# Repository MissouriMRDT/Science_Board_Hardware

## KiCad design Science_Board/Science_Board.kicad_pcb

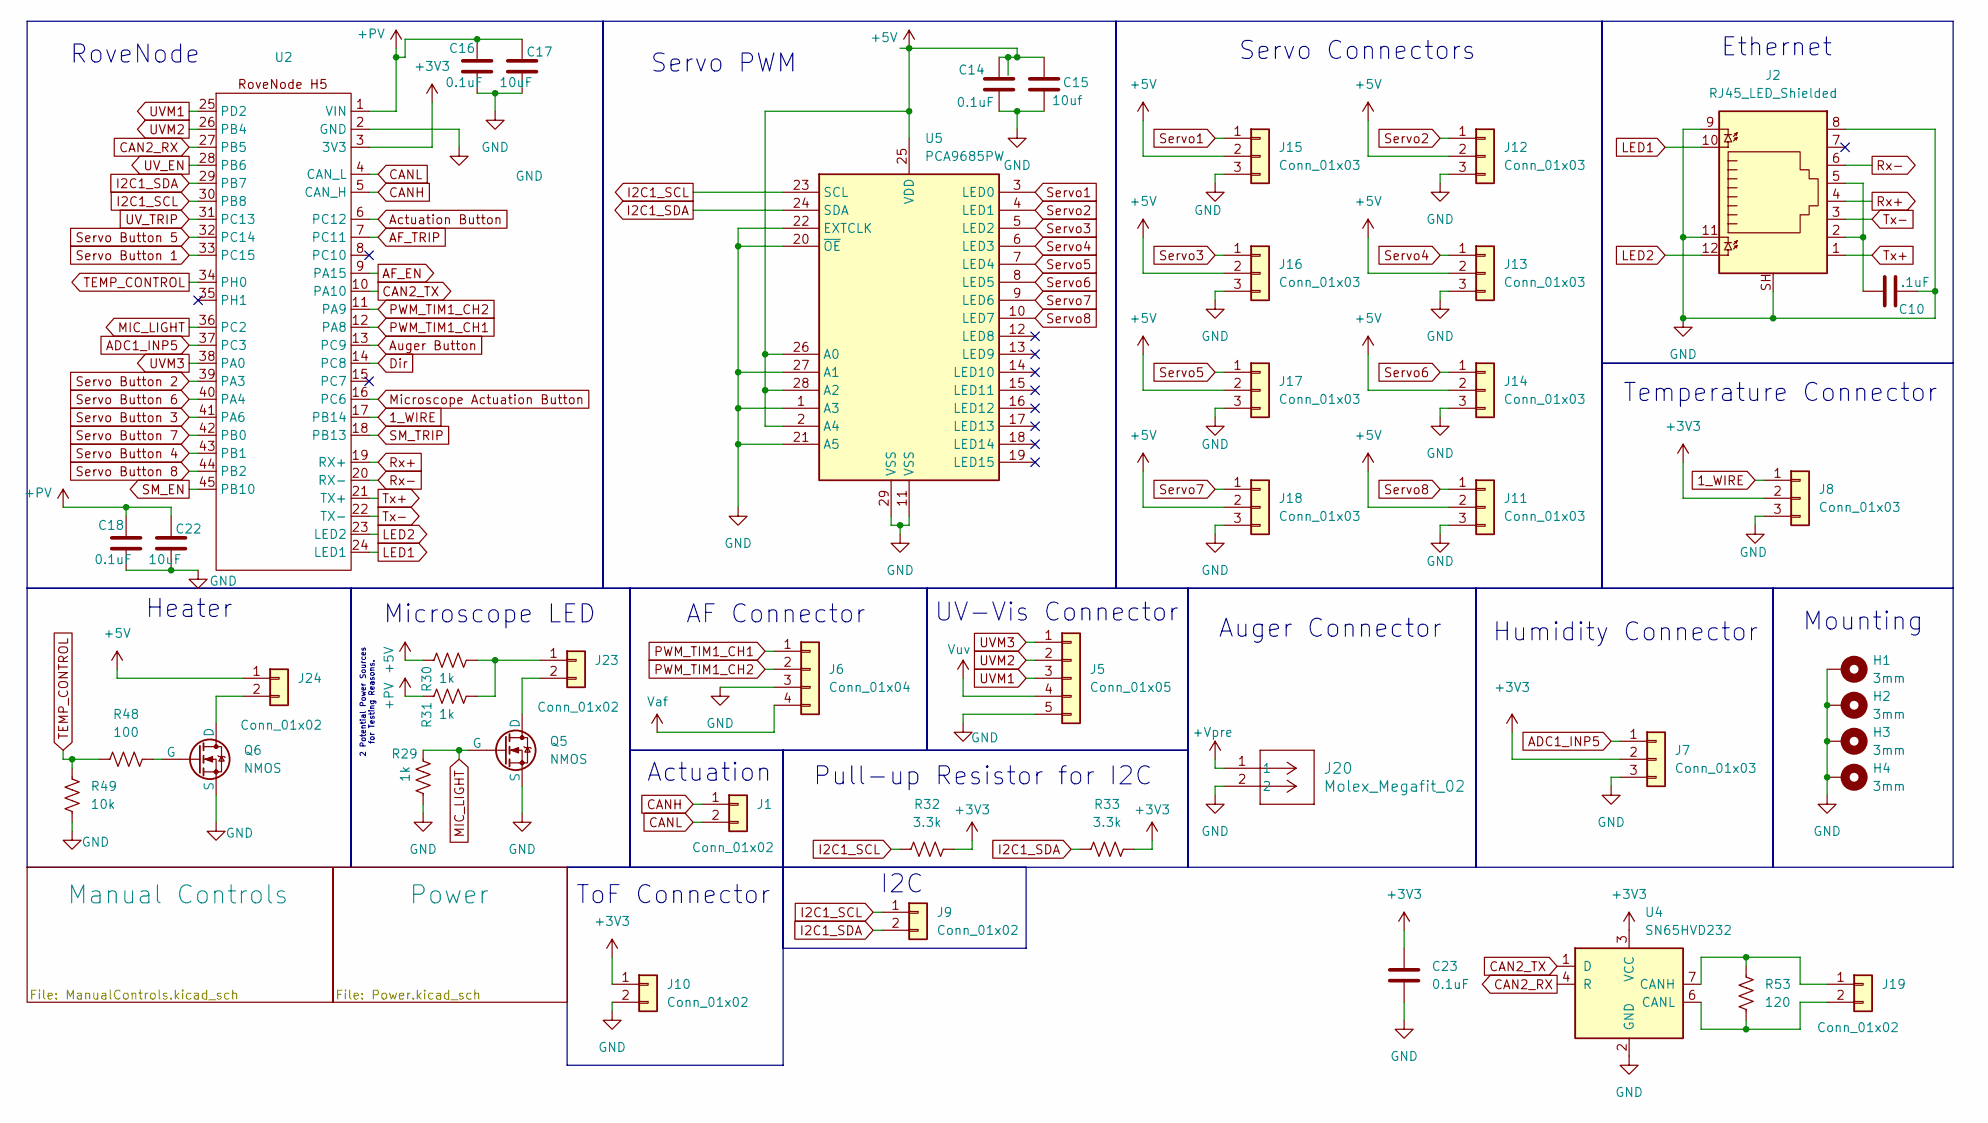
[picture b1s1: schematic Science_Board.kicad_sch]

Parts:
C10: .1uF; C_0603_1608Metric_Pad1.08x0.95mm_HandSolder
C14, C16, C18, C23: 0.1uF; C_0603_1608Metric_Pad1.08x0.95mm_HandSolder
C15: 10uf; C_1210_3225Metric_Pad1.33x2.70mm_HandSolder
C17, C22: 10uF; C_1210_3225Metric_Pad1.33x2.70mm_HandSolder
H1, H2, H3, H4: 3mm; 4_40_Hole_Pad_Via
J1, J9, J10, J19, J23, J24: Conn_01x02; JST_PH_B2B-PH-K_1x02_P2.00mm_Vertical
J2: RJ45_LED_Shielded; RJ45_Teensy
J5: Conn_01x05; JST_PH_B5B-PH-K_1x05_P2.00mm_Vertical
J6: Conn_01x04; JST_PH_B4B-PH-K_1x04_P2.00mm_Vertical
J7, J8, J11, J12, J13, J14, J15, J16, J17, J18: Conn_01x03; JST_PH_B3B-PH-K_1x03_P2.00mm_Vertical
J20: Molex_Megafit_02; MOLEX_MegaFit_02_Horizontal
Q5, Q6: NMOS; SOT-23-3
R29, R30, R31: 1k; R_0603_1608Metric_Pad0.98x0.95mm_HandSolder
R32, R33: 3.3k; R_0603_1608Metric_Pad0.98x0.95mm_HandSolder
R48: 100; R_0603_1608Metric_Pad0.98x0.95mm_HandSolder
R49: 10k; R_0603_1608Metric_Pad0.98x0.95mm_HandSolder
R53: 120; R_0603_1608Metric_Pad0.98x0.95mm_HandSolder
U2: RoveNode_H5
U4: SN65HVD232; SOIC-8_3.9x4.9mm_P1.27mm
U5: PCA9685PW; TSSOP-28_4.4x9.7mm_P0.65mm

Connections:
1_WIRE: J8.1, U2.17 (PB14)
+3V3: C23.1, J7.2, J8.2, J10.1, R32.2, R33.2, U2.3 (3V3), U4.3 (VCC); also elsewhere on the board
+5V: C14.1, C15.2, J11.2, J12.2, J13.2, J14.2, J15.2, J16.2, J17.2, J18.2, J24.1, R30.1, U5.2 (A4), U5.25 (VDD), U5.26 (A0), U5.28 (A2); also elsewhere on the board
+PV: C16.1, C17.2, C18.1, C22.2, R31.1, U2.1 (VIN); also elsewhere on the board
+Vpre: J20.1; also elsewhere on the board
ADC1_INP5: J7.1, U2.37 (PC3)
AF_EN: U2.9 (PA15); also elsewhere on the board
AF_TRIP: U2.7 (PC11); also elsewhere on the board
Actuation Button: U2.6 (PC12); also elsewhere on the board
Auger Button: U2.13 (PC9); also elsewhere on the board
CAN2_RX: U2.27 (PB5), U4.4 (R)
CAN2_TX: U2.10 (PA10), U4.1 (D)
CANH: J1.1, U2.5 (CAN_H)
CANL: J1.2, U2.4 (CAN_L)
Dir: U2.14 (PC8); also elsewhere on the board
GND: C10.2, C14.2, C15.1, C16.2, C17.1, C18.2, C22.1, C23.2, H1.1 (1_1), H2.1 (1_1), H3.1 (1_1), H4.1 (1_1), J2.8, J2.9, J2.11, J2.SH, J5.5, J6.3, J7.3, J8.3, J10.2, J11.3, J12.3, J13.3, J14.3, J15.3, J16.3, J17.3, J18.3, J20.2, Q5.3 (S), Q6.3 (S), R29.2, R49.1, U2.2 (GND), U4.2 (GND), U5.1 (A3), U5.11 (VSS), U5.20 (~OE), U5.21 (A5), U5.22 (EXTCLK), U5.27 (A1), U5.29 (VSS); also elsewhere on the board
I2C1_SCL: J9.1, R32.1, U2.30 (PB8), U5.23 (SCL)
I2C1_SDA: J9.2, R33.1, U2.29 (PB7), U5.24 (SDA)
LED1: J2.10, U2.24 (LED1)
LED2: J2.12, U2.23 (LED2)
MIC_LIGHT: Q5.2 (G), R29.1, U2.36 (PC2)
Microscope Actuation Button: U2.16 (PC6); also elsewhere on the board
unnamed: C10.1, J2.2, J2.5
unnamed: J19.1, R53.1, U4.7 (CANH)
unnamed: J19.2, R53.2, U4.6 (CANL)
unnamed: J23.1, R30.2, R31.2
unnamed: J23.2, Q5.1 (D)
unnamed: J24.2, Q6.1 (D)
unnamed: Q6.2 (G), R48.2
PWM_TIM1_CH1: J6.1, U2.12 (PA8)
PWM_TIM1_CH2: J6.2, U2.11 (PA9)
Rx+: J2.4, U2.19 (RX+)
Rx-: J2.6, U2.20 (RX-)
SM_EN: U2.45 (PB10); also elsewhere on the board
SM_TRIP: U2.18 (PB13); also elsewhere on the board
Servo1: J15.1, U5.3 (LED0)
Servo2: J12.1, U5.4 (LED1)
Servo3: J16.1, U5.5 (LED2)
Servo4: J13.1, U5.6 (LED3)
Servo5: J17.1, U5.7 (LED4)
Servo6: J14.1, U5.8 (LED5)
Servo7: J18.1, U5.9 (LED6)
Servo8: J11.1, U5.10 (LED7)
Servo Button 1: U2.33 (PC15); also elsewhere on the board
Servo Button 2: U2.39 (PA3); also elsewhere on the board
Servo Button 3: U2.41 (PA6); also elsewhere on the board
Servo Button 4: U2.43 (PB1); also elsewhere on the board
Servo Button 5: U2.32 (PC14); also elsewhere on the board
Servo Button 6: U2.40 (PA4); also elsewhere on the board
Servo Button 7: U2.42 (PB0); also elsewhere on the board
Servo Button 8: U2.44 (PB2); also elsewhere on the board
TEMP_CONTROL: R48.1, R49.2, U2.34 (PH0)
Tx+: J2.1, U2.21 (TX+)
Tx-: J2.3, U2.22 (TX-)
UVM1: J5.3, U2.25 (PD2)
UVM2: J5.2, U2.26 (PB4)
UVM3: J5.1, U2.38 (PA0)
UV_EN: U2.28 (PB6); also elsewhere on the board
UV_TRIP: U2.31 (PC13); also elsewhere on the board
Vaf: J6.4; also elsewhere on the board
Vuv: J5.4; also elsewhere on the board

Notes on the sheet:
UV-Vis Connector
Servo Connectors
Auger Connector
Temperature Connector
Servo PWM
ToF Connector
AF Connector
Microscope LED
RoveNode
Heater
Pull-up Resistor for I2C
Ethernet
Mounting
2 Potential Power Sources for Testing Reasons.
Actuation
I2C
Humidity Connector

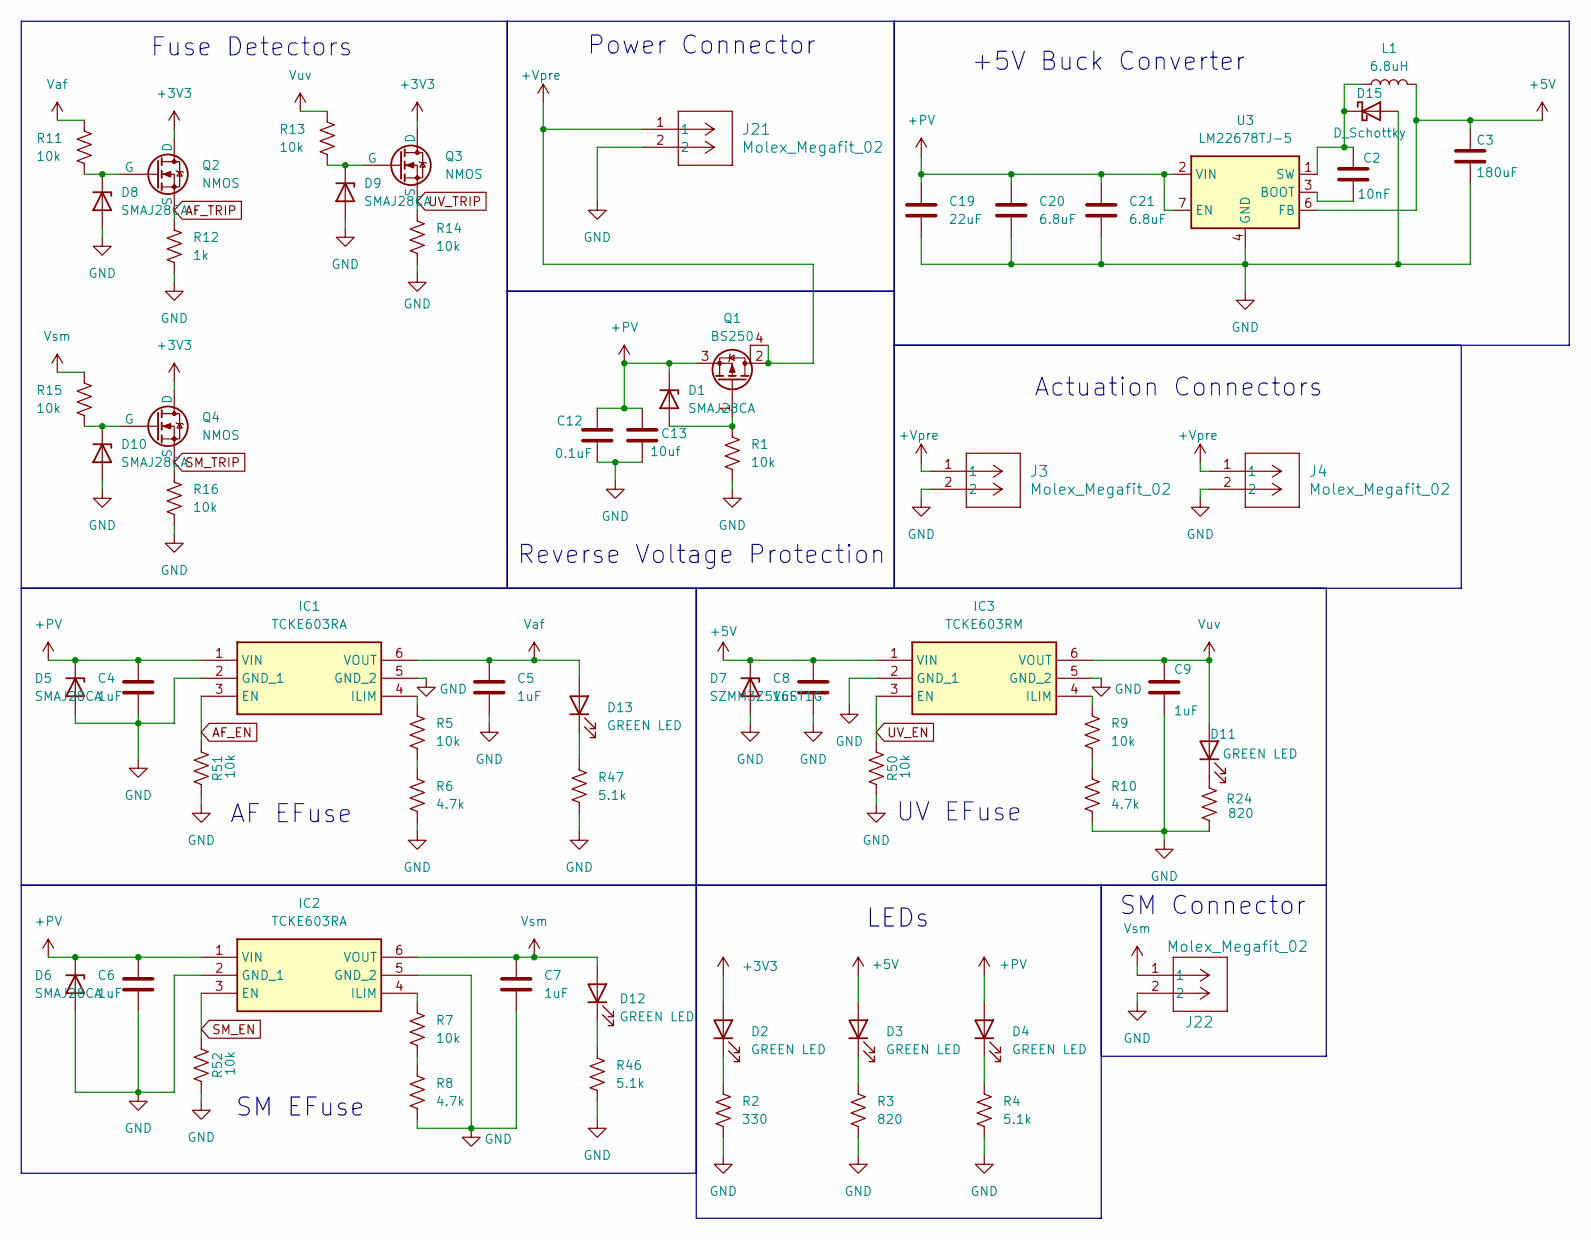
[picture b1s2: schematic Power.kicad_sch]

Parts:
C2: 10nF; C_0603_1608Metric_Pad1.08x0.95mm_HandSolder
C3: 180uF; CAP_EEEFNE181XUL
C4, C5, C6, C7, C8, C9: 1uF; C_0603_1608Metric_Pad1.08x0.95mm_HandSolder
C12: 0.1uF; C_0603_1608Metric_Pad1.08x0.95mm_HandSolder
C13: 10uf; C_1210_3225Metric_Pad1.33x2.70mm_HandSolder
C19: 22uF; C_1210_3225Metric_Pad1.33x2.70mm_HandSolder
C20, C21: 6.8uF; C_1206_3216Metric_Pad1.33x1.80mm_HandSolder
D1, D8, D9, D10: SMAJ28CA; D_SOD-123
D2, D3, D4, D11, D12, D13: GREEN LED; LED_0603_1608Metric_Pad1.05x0.95mm_HandSolder
D5, D6: SMAJ28CA; D_SMA_Handsoldering
D7: SZMM3Z5V6ST1G; D_SOD-323_HandSoldering
D15: D_Schottky; D_SOD-128
IC1, IC2: TCKE603RA; TCKE602RM; Manufacturer_Part_Number TCKE602RM
IC3: TCKE603RM; TCKE602RM; Manufacturer_Part_Number TCKE602RM
J3, J4, J21, J22: Molex_Megafit_02; MOLEX_MegaFit_02_Horizontal
L1: 6.8uH; L_Bourns_SRN8040TA
Q1: BS250; SOT-223
Q2, Q3, Q4: NMOS; SOT-23-3
R1, R5, R7, R9, R11, R13, R14, R15, R16: 10k; R_0603_1608Metric_Pad0.98x0.95mm_HandSolder
R2: 330; R_0603_1608Metric_Pad0.98x0.95mm_HandSolder
R3, R24: 820; R_0603_1608Metric_Pad0.98x0.95mm_HandSolder
R4, R46, R47: 5.1k; R_0603_1608Metric_Pad0.98x0.95mm_HandSolder
R6, R8, R10: 4.7k; R_0603_1608Metric_Pad0.98x0.95mm_HandSolder
R12: 1k; R_0603_1608Metric_Pad0.98x0.95mm_HandSolder
R50, R51, R52: 10k
U3: LM22678TJ-5; TO-263-7_TabPin8

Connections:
+3V3: D2.2 (A), Q2.1 (D), Q3.1 (D), Q4.1 (D); also elsewhere on the board
+5V: C3.1, C8.1, D3.2 (A), D7.1 (K), IC3.1 (VIN), L1.2, U3.6 (FB); also elsewhere on the board
+PV: C4.1, C6.1, C12.1, C13.2, C19.1, C20.1, C21.1, D1.1 (K), D4.2 (A), D5.1 (K), D6.1 (K), IC1.1 (VIN), IC2.1 (VIN), Q1.3 (S), U3.2 (VIN), U3.7 (EN); also elsewhere on the board
+Vpre: J3.1, J4.1, J21.1, Q1.2 (D), Q1.4 (D); also elsewhere on the board
AF_EN: IC1.3 (EN), R51.1; also elsewhere on the board
AF_TRIP: Q2.3 (S), R12.1; also elsewhere on the board
GND: C3.2, C4.2, C5.2, C6.2, C7.2, C8.2, C9.2, C12.2, C13.1, C19.2, C20.2, C21.2, D5.2 (A), D6.2 (A), D7.2 (A), D8.2 (A), D9.2 (A), D10.2 (A), D15.2 (A), IC1.2 (GND_1), IC1.5 (GND_2), IC2.2 (GND_1), IC2.5 (GND_2), IC3.2 (GND_1), IC3.5 (GND_2), J3.2, J4.2, J21.2, J22.2, R1.1, R2.2, R3.2, R4.2, R6.2, R8.2, R10.2, R12.2, R14.2, R16.2, R24.2, R46.2, R47.2, R50.2, R51.2, R52.2, U3.4 (GND), U3.8 (GND); also elsewhere on the board
unnamed: D1.2 (A), Q1.1 (G), R1.2
unnamed: D2.1 (K), R2.1
unnamed: D3.1 (K), R3.1
unnamed: D4.1 (K), R4.1
unnamed: D8.1 (K), Q2.2 (G), R11.2
unnamed: D9.1 (K), Q3.2 (G), R13.2
unnamed: D10.1 (K), Q4.2 (G), R15.2
unnamed: D11.1 (K), R24.1
unnamed: D12.1 (K), R46.1
unnamed: D13.1 (K), R47.1
unnamed: C2.1, D15.1 (K), L1.1, U3.1 (SW)
unnamed: IC1.4 (ILIM), R5.1
unnamed: IC2.4 (ILIM), R7.1
unnamed: IC3.4 (ILIM), R9.1
unnamed: R5.2, R6.1
unnamed: R7.2, R8.1
unnamed: R9.2, R10.1
unnamed: C2.2, U3.3 (BOOT)
SM_EN: IC2.3 (EN), R52.1; also elsewhere on the board
SM_TRIP: Q4.3 (S), R16.1; also elsewhere on the board
UV_EN: IC3.3 (EN), R50.1; also elsewhere on the board
UV_TRIP: Q3.3 (S), R14.1; also elsewhere on the board
Vaf: C5.1, D13.2 (A), IC1.6 (VOUT), R11.1; also elsewhere on the board
Vsm: C7.1, D12.2 (A), IC2.6 (VOUT), J22.1, R15.1
Vuv: C9.1, D11.2 (A), IC3.6 (VOUT), R13.1; also elsewhere on the board

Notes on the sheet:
Reverse Voltage Protection
Fuse Detectors
Power Connector
+5V Buck Converter
AF EFuse
SM EFuse
UV EFuse
Actuation Connectors
LEDs
SM Connector

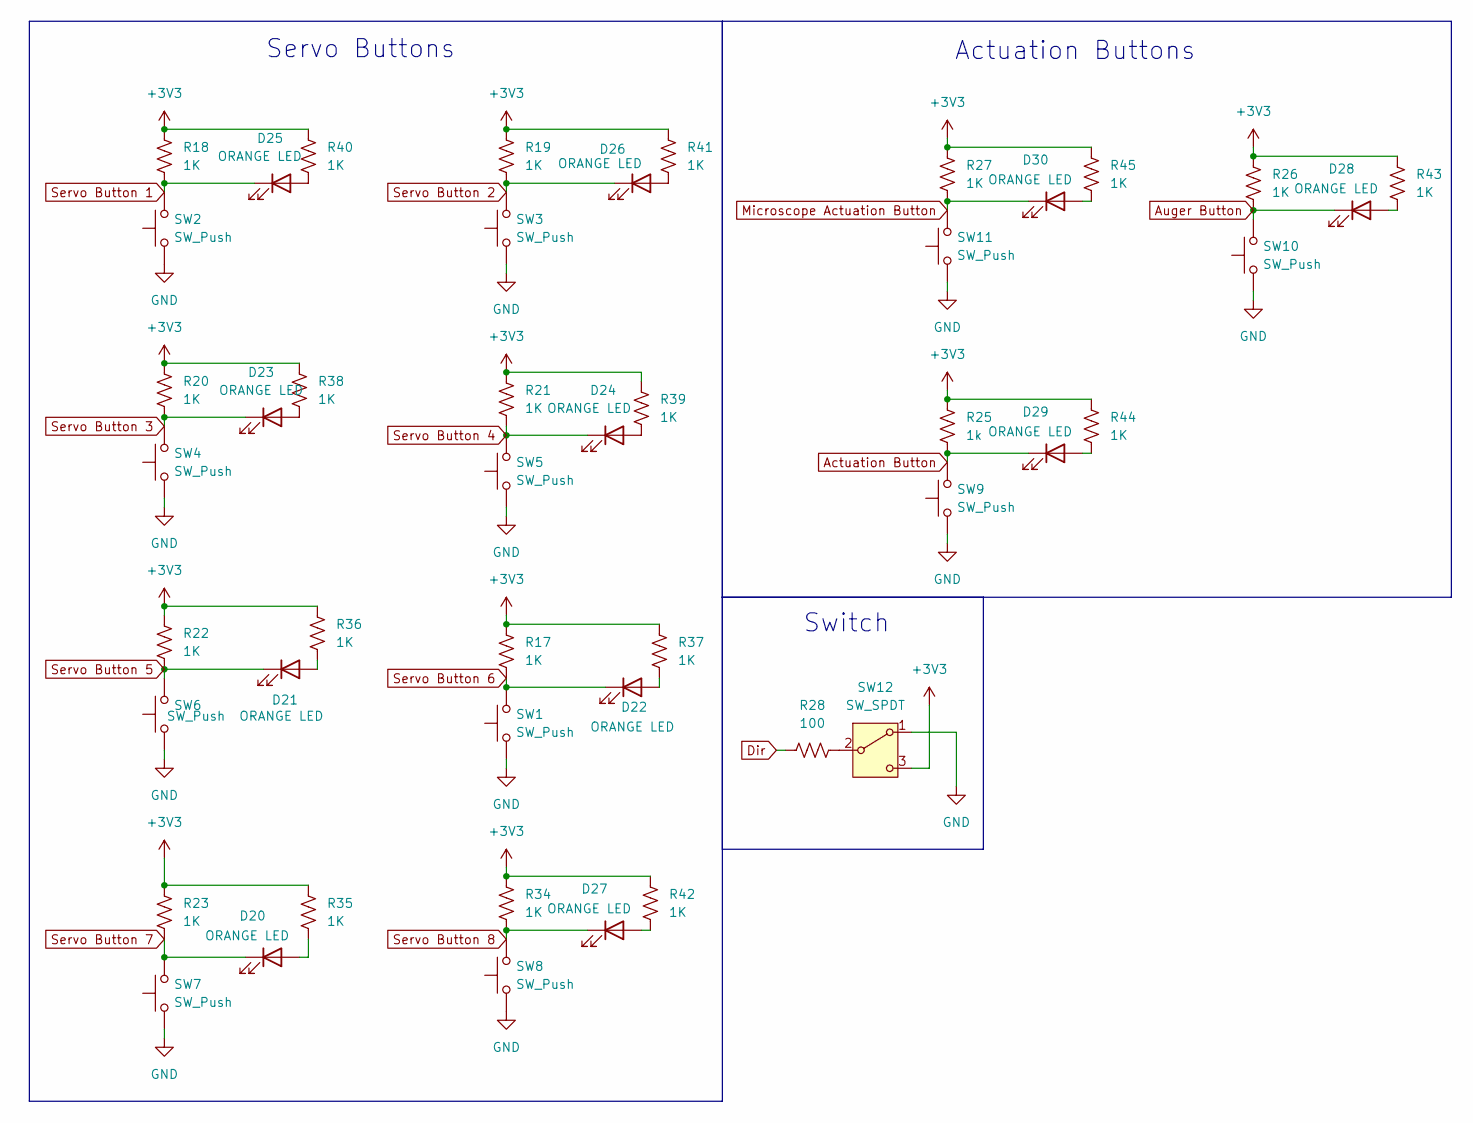
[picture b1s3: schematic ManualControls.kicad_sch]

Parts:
D20, D21, D22, D23, D24, D25, D26, D27, D28, D29, D30: ORANGE LED; LED_0603_1608Metric_Pad1.05x0.95mm_HandSolder
R17, R18, R19, R20, R21, R22, R23, R26, R27, R34, R35, R36, R37, R38, R39, R40, R41, R42, R43, R44, R45: 1K; R_0603_1608Metric_Pad0.98x0.95mm_HandSolder
R25: 1k; R_0603_1608Metric_Pad0.98x0.95mm_HandSolder
R28: 100; R_0603_1608Metric_Pad0.98x0.95mm_HandSolder
SW1, SW2, SW3, SW4, SW5, SW6, SW7, SW8, SW9, SW10, SW11: SW_Push; SW_SPST_TL3305A
SW12: SW_SPDT; SW_Slide_SPDT_Straight_CK_OS102011MS2Q

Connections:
+3V3: R17.1, R18.1, R19.1, R20.1, R21.1, R22.1, R23.1, R25.1, R26.1, R27.1, R34.1, R35.1, R36.1, R37.1, R38.1, R39.1, R40.1, R41.1, R42.1, R43.1, R44.1, R45.1, SW12.3 (C); also elsewhere on the board
Actuation Button: D29.1 (K), R25.2, SW9.2; also elsewhere on the board
Auger Button: D28.1 (K), R26.2, SW10.2; also elsewhere on the board
Dir: R28.1; also elsewhere on the board
GND: SW1.1, SW2.1, SW3.1, SW4.1, SW5.1, SW6.1, SW7.1, SW8.1, SW9.1, SW10.1, SW11.1, SW12.1 (A); also elsewhere on the board
Microscope Actuation Button: D30.1 (K), R27.2, SW11.2; also elsewhere on the board
unnamed: D20.2 (A), R35.2
unnamed: D21.2 (A), R36.2
unnamed: D22.2 (A), R37.2
unnamed: D23.2 (A), R38.2
unnamed: D24.2 (A), R39.2
unnamed: D25.2 (A), R40.2
unnamed: D26.2 (A), R41.2
unnamed: D27.2 (A), R42.2
unnamed: D28.2 (A), R43.2
unnamed: D29.2 (A), R44.2
unnamed: D30.2 (A), R45.2
unnamed: R28.2, SW12.2 (B)
Servo Button 1: D25.1 (K), R18.2, SW2.2; also elsewhere on the board
Servo Button 2: D26.1 (K), R19.2, SW3.2; also elsewhere on the board
Servo Button 3: D23.1 (K), R20.2, SW4.2; also elsewhere on the board
Servo Button 4: D24.1 (K), R21.2, SW5.2; also elsewhere on the board
Servo Button 5: D21.1 (K), R22.2, SW6.2; also elsewhere on the board
Servo Button 6: D22.1 (K), R17.2, SW1.2; also elsewhere on the board
Servo Button 7: D20.1 (K), R23.2, SW7.2; also elsewhere on the board
Servo Button 8: D27.1 (K), R34.2, SW8.2; also elsewhere on the board

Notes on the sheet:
Actuation Buttons
Switch
Servo Buttons

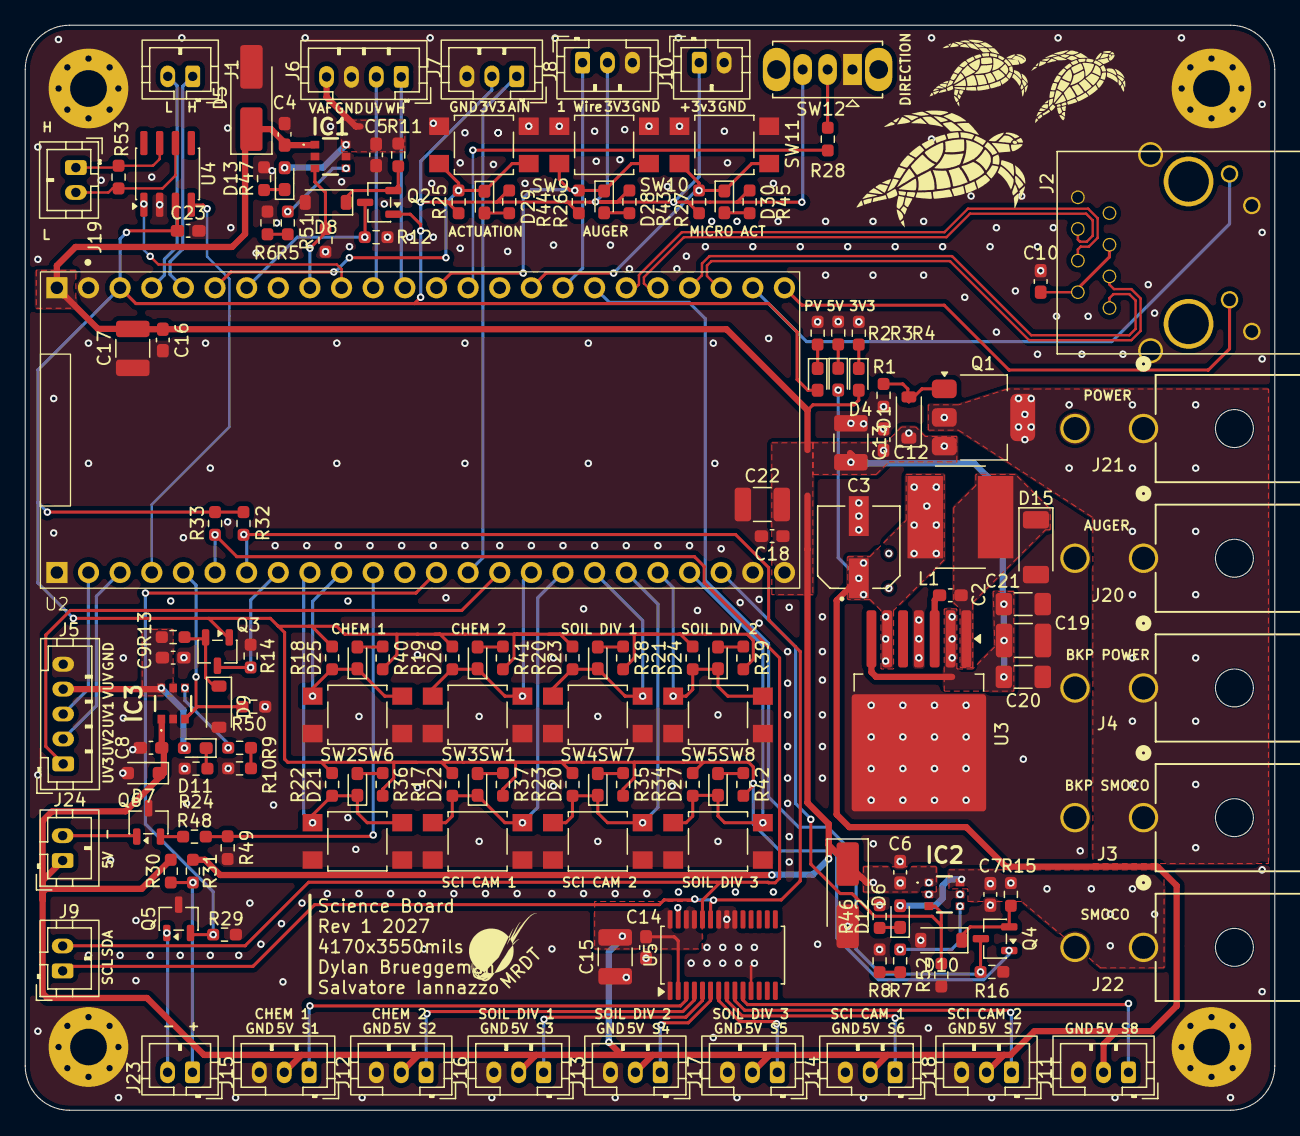
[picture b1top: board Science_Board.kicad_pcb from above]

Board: 4 copper layers, 100.3 x 87.1 mm, 153 parts (0 on the bottom side), 92 nets.
